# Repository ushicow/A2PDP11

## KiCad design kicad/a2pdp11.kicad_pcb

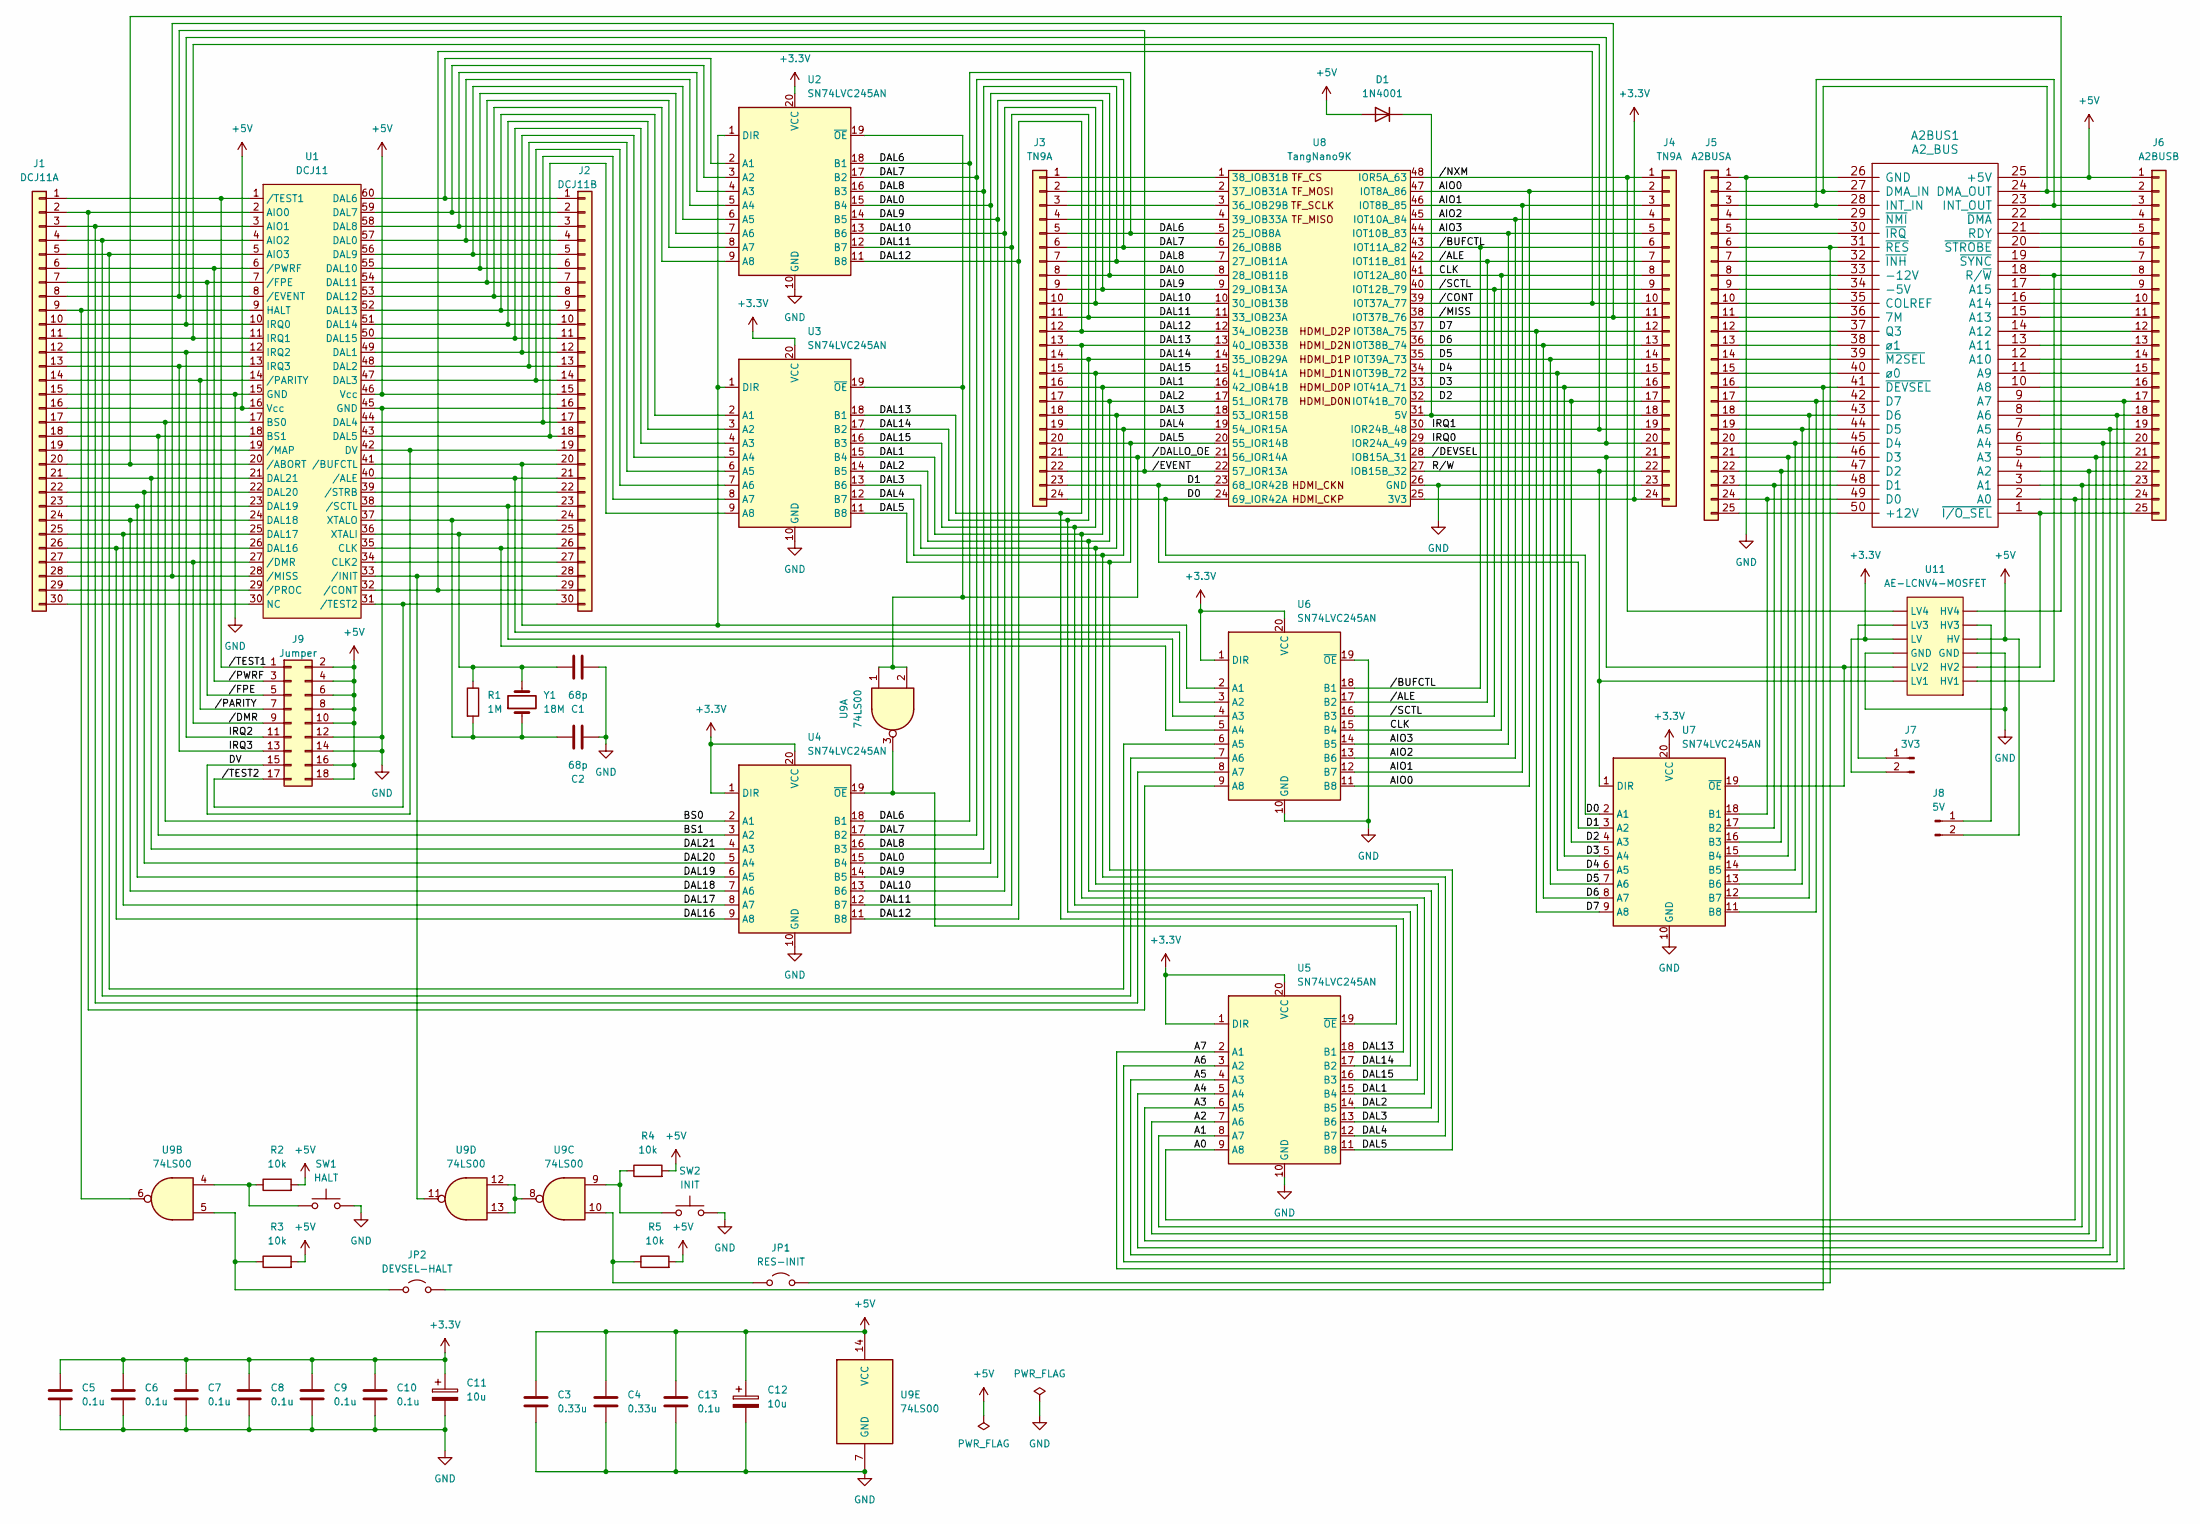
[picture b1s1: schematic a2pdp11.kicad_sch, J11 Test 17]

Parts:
A2BUS1: A2_BUS; BUS_A2
C1, C2: 68p; C_Disc_D3.0mm_W1.6mm_P2.54mm
C3, C4: 0.33u; C_Disc_D4.3mm_W1.9mm_P5.08mm
C5, C6, C7, C8, C9, C10, C13: 0.1u; C_Disc_D4.3mm_W1.9mm_P5.08mm
C11, C12: 10u; CP_Radial_D5.0mm_P2.00mm
D1: 1N4001; D_DO-41_SOD81_P10.16mm_Horizontal
J1: DCJ11A; PinHeader_1x30_P2.54mm_Vertical
J2: DCJ11B; PinHeader_1x30_P2.54mm_Vertical
J3, J4: TN9A; PinHeader_1x24_P2.54mm_Vertical
J5: A2BUSA; PinHeader_1x25_P2.54mm_Vertical
J6: A2BUSB; PinHeader_1x25_P2.54mm_Vertical
J7: 3V3; PinHeader_1x02_P2.54mm_Vertical
J8: 5V; PinHeader_1x02_P2.54mm_Vertical
J9: Jumper; PinHeader_2x09_P2.54mm_Vertical
JP1: RES-INIT; PinHeader_2x01_P2.54mm_Vertical
JP2: DEVSEL-HALT; PinHeader_2x01_P2.54mm_Vertical
R1: 1M; R_Axial_DIN0207_L6.3mm_D2.5mm_P10.16mm_Horizontal
R2, R3, R4, R5: 10k; R_Axial_DIN0207_L6.3mm_D2.5mm_P10.16mm_Horizontal
SW1: HALT; SW_PUSH_6mm_H4.3mm
SW2: INIT; SW_PUSH_6mm_H4.3mm
U1: DCJ11
U2, U3, U4, U5, U6, U7: SN74LVC245AN; DIP-20_W7.62mm
U8: TangNano9K
U9: 74LS00; DIP-14_W7.62mm_Socket
U11: AE-LCNV4-MOSFET
Y1: 18M; Crystal_HC18-U_Horizontal

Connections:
+3.3V: C5.1, C6.1, C7.1, C8.1, C9.1, C10.1, C11.1, J4.24, J7.2, U2.20 (VCC), U3.20 (VCC), U4.1 (DIR), U4.20 (VCC), U5.1 (DIR), U5.20 (VCC), U6.1 (DIR), U6.20 (VCC), U7.20 (VCC), U8.25 (3V3), U11.9 (LV)
+5V: A2BUS1.25 (+5V), C3.1, C4.1, C12.1, C13.1, D1.2 (A), J1.16, J2.15, J6.1, J8.2, J9.2, J9.4, J9.6, J9.8, J9.10, J9.16, J9.18, R2.2, R3.2, R4.2, R5.2, U1.16 (Vcc), U1.46 (Vcc), U9.14 (VCC), U11.4 (HV)
/A0: A2BUS1.2 (A0), J6.24, U5.9 (A8)
/A1: A2BUS1.3 (A1), J6.23, U5.8 (A7)
/A2: A2BUS1.4 (A2), J6.22, U5.7 (A6)
/A3: A2BUS1.5 (A3), J6.21, U5.6 (A5)
/A4: A2BUS1.6 (A4), J6.20, U5.5 (A4)
/A5: A2BUS1.7 (A5), J6.19, U5.4 (A3)
/A6: A2BUS1.8 (A6), J6.18, U5.3 (A2)
/A7: A2BUS1.9 (A7), J6.17, U5.2 (A1)
/AIO0: J4.2, U6.11 (B8), U8.47 (IOT8A_86)
/AIO1: J4.3, U6.12 (B7), U8.46 (IOT8B_85)
/AIO2: J4.4, U6.13 (B6), U8.45 (IOT10A_84)
/AIO3: J4.5, U6.14 (B5), U8.44 (IOT10B_83)
/BS0: J1.17, U1.17 (BS0), U4.2 (A1)
/BS1: J1.18, U1.18 (BS1), U4.3 (A2)
/CLK: J4.8, U6.15 (B4), U8.41 (IOT12A_80)
/D0: J3.24, U7.2 (A1), U8.24 (69_IOR42A)
/D1: J3.23, U7.3 (A2), U8.23 (68_IOR42B)
/D2: J4.17, U7.4 (A3), U8.32 (IOT41B_70)
/D3: J4.16, U7.5 (A4), U8.33 (IOT41A_71)
/D4: J4.15, U7.6 (A5), U8.34 (IOT39B_72)
/D5: J4.14, U7.7 (A6), U8.35 (IOT39A_73)
/D6: J4.13, U7.8 (A7), U8.36 (IOT38B_74)
/D7: J4.12, U7.9 (A8), U8.37 (IOT38A_75)
/DAL0: J3.8, U2.15 (B4), U4.15 (B4), U8.8 (28_IOB11B)
/DAL1: J3.16, U3.15 (B4), U5.15 (B4), U8.16 (42_IOB41B)
/DAL2: J3.17, U3.14 (B5), U5.14 (B5), U8.17 (51_IOR17B)
/DAL3: J3.18, U3.13 (B6), U5.13 (B6), U8.18 (53_IOR15B)
/DAL4: J3.19, U3.12 (B7), U5.12 (B7), U8.19 (54_IOR15A)
/DAL5: J3.20, U3.11 (B8), U5.11 (B8), U8.20 (55_IOR14B)
/DAL6: J3.5, U2.18 (B1), U4.18 (B1), U8.5 (25_IOB8A)
/DAL7: J3.6, U2.17 (B2), U4.17 (B2), U8.6 (26_IOB8B)
/DAL8: J3.7, U2.16 (B3), U4.16 (B3), U8.7 (27_IOB11A)
/DAL9: J3.9, U2.14 (B5), U4.14 (B5), U8.9 (29_IOB13A)
/DAL10: J3.10, U2.13 (B6), U4.13 (B6), U8.10 (30_IOB13B)
/DAL11: J3.11, U2.12 (B7), U4.12 (B7), U8.11 (33_IOB23A)
/DAL12: J3.12, U2.11 (B8), U4.11 (B8), U8.12 (34_IOB23B)
/DAL13: J3.13, U3.18 (B1), U5.18 (B1), U8.13 (40_IOB33B)
/DAL14: J3.14, U3.17 (B2), U5.17 (B2), U8.14 (35_IOB29A)
/DAL15: J3.15, U3.16 (B3), U5.16 (B3), U8.15 (41_IOB41A)
/DAL16: J1.26, U1.26 (DAL16), U4.9 (A8)
/DAL17: J1.25, U1.25 (DAL17), U4.8 (A7)
/DAL18: J1.24, U1.24 (DAL18), U4.7 (A6)
/DAL19: J1.23, U1.23 (DAL19), U4.6 (A5)
/DAL20: J1.22, U1.22 (DAL20), U4.5 (A4)
/DAL21: J1.21, U1.21 (DAL21), U4.4 (A3)
/DV: J2.19, J9.15, U1.42 (DV)
/IRQ0: J1.10, J4.20, U1.10 (IRQ0), U8.29 (IOR24A_49)
/IRQ1: J1.11, J4.19, U1.11 (IRQ1), U8.30 (IOR24B_48)
/IRQ2: J1.12, J9.11, U1.12 (IRQ2)
/IRQ3: J1.13, J9.13, U1.13 (IRQ3)
/R/W: J4.22, U7.1 (DIR), U8.27 (IOB15B_32), U11.12 (LV1)
//ALE: J4.7, U6.17 (B2), U8.42 (IOT11B_81)
//BUFCTL: J4.6, U6.18 (B1), U8.43 (IOT11A_82)
//CONT: J2.29, J4.10, U1.32 (/CONT), U8.39 (IOT37A_77)
//DALLO_OE: J3.21, U2.19 (~OE), U3.19 (~OE), U8.21 (56_IOR14A), U9.1, U9.2
//DEVSEL: J4.21, U7.19 (~OE), U8.28 (IOB15A_31), U11.11 (LV2)
//DMR: J1.27, J9.9, U1.27 (/DMR)
//EVENT: J1.8, J3.22, U1.8 (/EVENT), U8.22 (57_IOR13A)
//FPE: J1.7, J9.5, U1.7 (/FPE)
//MISS: J1.28, J4.11, U1.28 (/MISS), U8.38 (IOT37B_76)
//NXM: J4.1, U8.48 (IOR5A_63), U11.7 (LV4)
//PARITY: J1.14, J9.7, U1.14 (/PARITY)
//PWRF: J1.6, J9.3, U1.6 (/PWRF)
//SCTL: J4.9, U6.16 (B3), U8.40 (IOT12B_79)
//TEST1: J1.1, J9.1, U1.1 (/TEST1)
//TEST2: J2.30, J9.17, U1.31 (/TEST2)
GND: A2BUS1.26 (GND), C1.2, C2.2, C3.2, C4.2, C5.2, C6.2, C7.2, C8.2, C9.2, C10.2, C11.2, C12.2, C13.2, J1.15, J2.16, J4.23, J5.1, J9.12, J9.14, SW1.2, SW2.2, U1.15 (GND), U1.45 (GND), U2.10 (GND), U3.10 (GND), U4.10 (GND), U5.10 (GND), U6.10 (GND), U6.19 (~OE), U7.10 (GND), U8.26 (GND), U9.7 (GND), U11.3 (GND), U11.10 (GND)
unnamed: A2BUS1.36 (7M), J5.11
unnamed: A2BUS1.50 (+12V), J5.25
unnamed: A2BUS1.34 (-5V), J5.9
unnamed: A2BUS1.33 (-12V), J5.8
unnamed: A2BUS1.10 (A8), J6.16
unnamed: A2BUS1.11 (A9), J6.15
unnamed: A2BUS1.12 (A10), J6.14
unnamed: A2BUS1.13 (A11), J6.13
unnamed: A2BUS1.14 (A12), J6.12
unnamed: A2BUS1.15 (A13), J6.11
unnamed: A2BUS1.16 (A14), J6.10
unnamed: A2BUS1.17 (A15), J6.9
unnamed: A2BUS1.35 (COLREF), J5.10
unnamed: A2BUS1.49 (D0), J5.24, U7.18 (B1)
unnamed: A2BUS1.48 (D1), J5.23, U7.17 (B2)
unnamed: A2BUS1.47 (D2), J5.22, U7.16 (B3)
unnamed: A2BUS1.46 (D3), J5.21, U7.15 (B4)
unnamed: A2BUS1.45 (D4), J5.20, U7.14 (B5)
unnamed: A2BUS1.44 (D5), J5.19, U7.13 (B6)
unnamed: A2BUS1.43 (D6), J5.18, U7.12 (B7)
unnamed: A2BUS1.42 (D7), J5.17, U7.11 (B8)
unnamed: A2BUS1.24 (DMA_OUT), A2BUS1.27 (DMA_IN), J5.2, J6.2
unnamed: A2BUS1.23 (INT_OUT), A2BUS1.28 (INT_IN), J5.3, J6.3
unnamed: A2BUS1.37 (Q3), J5.12
unnamed: A2BUS1.21 (RDY), J6.5
unnamed: A2BUS1.18 (R/~W), J6.8, U11.1 (HV1)
unnamed: A2BUS1.41 (~DEVSEL), J5.16, JP2.2 (B)
unnamed: A2BUS1.22 (~DMA), J6.4
unnamed: A2BUS1.32 (~INH), J5.7
unnamed: A2BUS1.30 (~IRQ), J5.5
unnamed: A2BUS1.1 (~I/O_SEL), J6.25, U11.2 (HV2)
unnamed: A2BUS1.39 (~M2SEL), J5.14
unnamed: A2BUS1.29 (~NMI), J5.4
unnamed: A2BUS1.31 (~RES), J5.6, JP1.2 (B)
unnamed: A2BUS1.20 (~STROBE), J6.6
unnamed: A2BUS1.19 (~SYNC), J6.7
unnamed: A2BUS1.40 (ø0), J5.15
unnamed: A2BUS1.38 (ø1), J5.13
unnamed: D1.1 (K), J4.18, U8.31 (5V)
unnamed: J1.2, U1.2 (AIO0), U6.9 (A8)
unnamed: J1.3, U1.3 (AIO1), U6.8 (A7)
unnamed: J1.4, U1.4 (AIO2), U6.7 (A6)
unnamed: J1.5, U1.5 (AIO3), U6.6 (A5)
unnamed: J1.9, U1.9 (HALT), U9.6
unnamed: J1.19, U1.19 (/MAP)
unnamed: J1.20, U1.20 (/ABORT), U11.6 (HV4)
unnamed: J1.29, U1.29 (/PROC)
unnamed: J1.30, U1.30 (NC)
unnamed: J2.1, U1.60 (DAL6), U2.2 (A1)
unnamed: J2.2, U1.59 (DAL7), U2.3 (A2)
unnamed: J2.3, U1.58 (DAL8), U2.4 (A3)
unnamed: J2.4, U1.57 (DAL0), U2.5 (A4)
unnamed: J2.5, U1.56 (DAL9), U2.6 (A5)
unnamed: J2.6, U1.55 (DAL10), U2.7 (A6)
unnamed: J2.7, U1.54 (DAL11), U2.8 (A7)
unnamed: J2.8, U1.53 (DAL12), U2.9 (A8)
unnamed: J2.9, U1.52 (DAL13), U3.2 (A1)
unnamed: J2.10, U1.51 (DAL14), U3.3 (A2)
unnamed: J2.11, U1.50 (DAL15), U3.4 (A3)
unnamed: J2.12, U1.49 (DAL1), U3.5 (A4)
unnamed: J2.13, U1.48 (DAL2), U3.6 (A5)
unnamed: J2.14, U1.47 (DAL3), U3.7 (A6)
unnamed: J2.17, U1.44 (DAL4), U3.8 (A7)
unnamed: J2.18, U1.43 (DAL5), U3.9 (A8)
unnamed: J2.20, U1.41 (/BUFCTL), U2.1 (DIR), U3.1 (DIR), U6.2 (A1)
unnamed: J2.21, U1.40 (/ALE), U6.3 (A2)
unnamed: J2.22, U1.39 (/STRB)
unnamed: J2.23, U1.38 (/SCTL), U6.4 (A3)
unnamed: C2.1, J2.24, R1.2, U1.37 (XTALO), Y1.1
unnamed: C1.1, J2.25, R1.1, U1.36 (XTALI), Y1.2
unnamed: J2.26, U1.35 (CLK), U6.5 (A4)
unnamed: J2.27, U1.34 (CLK2)
unnamed: J2.28, U1.33 (/INIT), U9.11
unnamed: J3.1, U8.1 (38_IOB31B)
unnamed: J3.2, U8.2 (37_IOB31A)
unnamed: J3.3, U8.3 (36_IOB29B)
unnamed: J3.4, U8.4 (39_IOB33A)
unnamed: J7.1, U11.8 (LV3)
unnamed: J8.1, U11.5 (HV3)
unnamed: JP1.1 (A), R5.1, U9.10
unnamed: JP2.1 (A), R3.1, U9.5
unnamed: R2.1, SW1.1, U9.4
unnamed: R4.1, SW2.1, U9.9
unnamed: U4.19 (~OE), U5.19 (~OE), U9.3
unnamed: U9.8, U9.12, U9.13

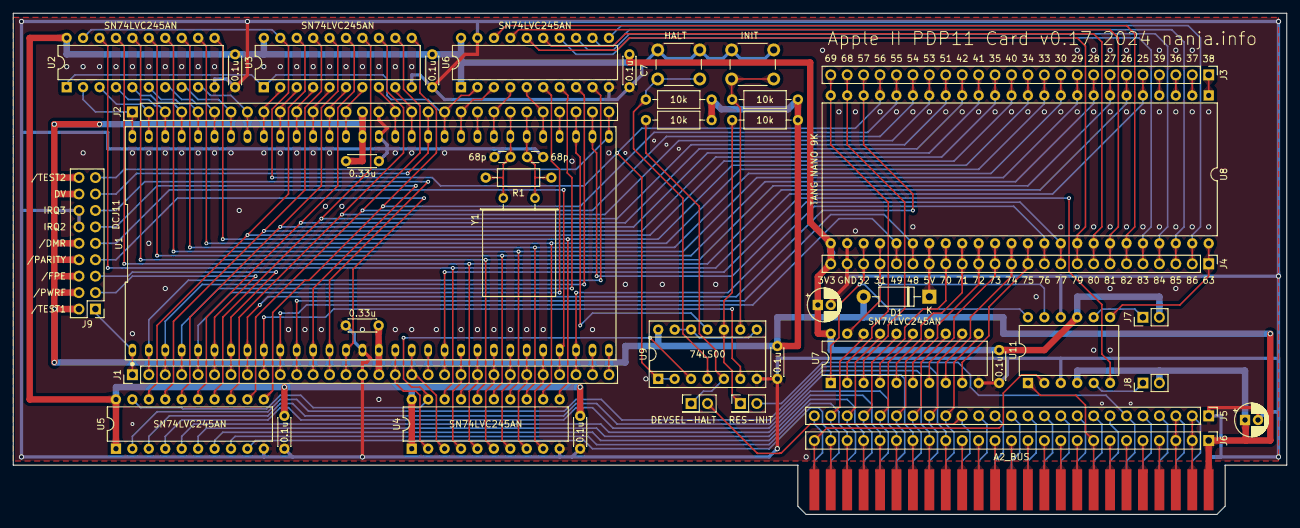
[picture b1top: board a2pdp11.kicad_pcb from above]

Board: 2 copper layers, 196.9 x 77.5 mm, 44 parts (0 on the bottom side), 154 nets.

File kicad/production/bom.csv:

Designator,Footprint,Quantity,Value,LCSC Part #
A1BUS1,BUS_A2,1,A2_BUS,
"C1, C2",C_Disc_D3.0mm_W1.6mm_P2.54mm,2,68p,
"C10, C13, C5, C6, C7, C8, C9",C_Disc_D4.3mm_W1.9mm_P5.08mm,7,0.1u,
"C11, C12",CP_Radial_D5.0mm_P2.00mm,2,10u,
"C3, C4",C_Disc_D4.3mm_W1.9mm_P5.08mm,2,0.33u,
D1,D_DO-41_SOD81_P10.16mm_Horizontal,1,1N4001,
J1,PinHeader_1x30_P2.54mm_Vertical,1,DCJ11A,
J10,PinSocket_2x03_P2.54mm_Vertical,1,~,
J2,PinHeader_1x30_P2.54mm_Vertical,1,DCJ11B,
"J3, J4",PinHeader_1x24_P2.54mm_Vertical,2,TN9A,
J5,PinHeader_1x25_P2.54mm_Vertical,1,A2BUSA,
J6,PinHeader_1x25_P2.54mm_Vertical,1,A2BUSB,
J7,PinHeader_1x02_P2.54mm_Vertical,1,3V3,
J8,PinHeader_1x02_P2.54mm_Vertical,1,5V,
J9,PinHeader_2x09_P2.54mm_Vertical,1,Jumper,
JP1,PinHeader_2x01_P2.54mm_Vertical,1,RES-INIT,
JP2,PinHeader_2x01_P2.54mm_Vertical,1,IOSEL-HALT,
R1,R_Axial_DIN0207_L6.3mm_D2.5mm_P10.16mm_Horizontal,1,1M,
"R2, R3, R4, R5",R_Axial_DIN0207_L6.3mm_D2.5mm_P10.16mm_Horizontal,4,10k,
SW1,SW_PUSH_6mm_H4.3mm,1,HALT,
SW2,SW_PUSH_6mm_H4.3mm,1,INIT,
U1,DCJ11,1,DCJ11,
U11,AE-LCNV4-MOSFET,1,AE-LCNV4-MOSFET,
"U2, U3, U4, U5, U6, U7",DIP-20_W7.62mm,6,SN74LVC245AN,
U8,TangNano9K,1,TangNano9K,
U9,DIP-14_W7.62mm_Socket,1,74LS00,
Y1,Crystal_HC18-U_Horizontal,1,18M,

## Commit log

2024-08-02 test2: bus read
2024-08-04 test3: mode 3 boot
2024-08-09 test4: NXM abort
2024-08-12 test5: Console ODT output
2024-08-25 test6: console ODT
2024-08-26 test7: 2KB ram
2024-09-01 test8: 8MB ram
2024-09-08 test9: Byte Data Write
2024-09-10 BASIC
2024-09-13 test10: Run BASIC
2024-09-15 mclk = 165MHz
2024-09-15 modify dal output
2024-09-16 optimize timing
2024-09-16 memory_clk = 165Mhz, clk_x2 = 54Mhz
2024-09-22 test11: Modify read timing
2024-10-22 add process config
2024-10-22 add kicad schematic
2024-10-22 add arduino
2024-10-22 chenge arduino directory
2024-10-23 aio multiplexed
2024-10-25 dalhi_oe_n = !dalhi_oe_n
2024-11-02 run BASIC, but unstable
2024-11-10 Apple II interface
2024-11-17 Change I/O signal to IOSEL
2024-11-24 chenge clock
2024-11-26 source clean up
2024-12-01 PC11 paper tape reader
2024-12-15 TEST18: PC11 paper tape reader
